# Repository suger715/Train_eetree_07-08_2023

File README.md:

# Train_eetree_07-08_2023
###From July to August 2023, I interned in some projects of Suzhou Hard Harvest Information Technology Company

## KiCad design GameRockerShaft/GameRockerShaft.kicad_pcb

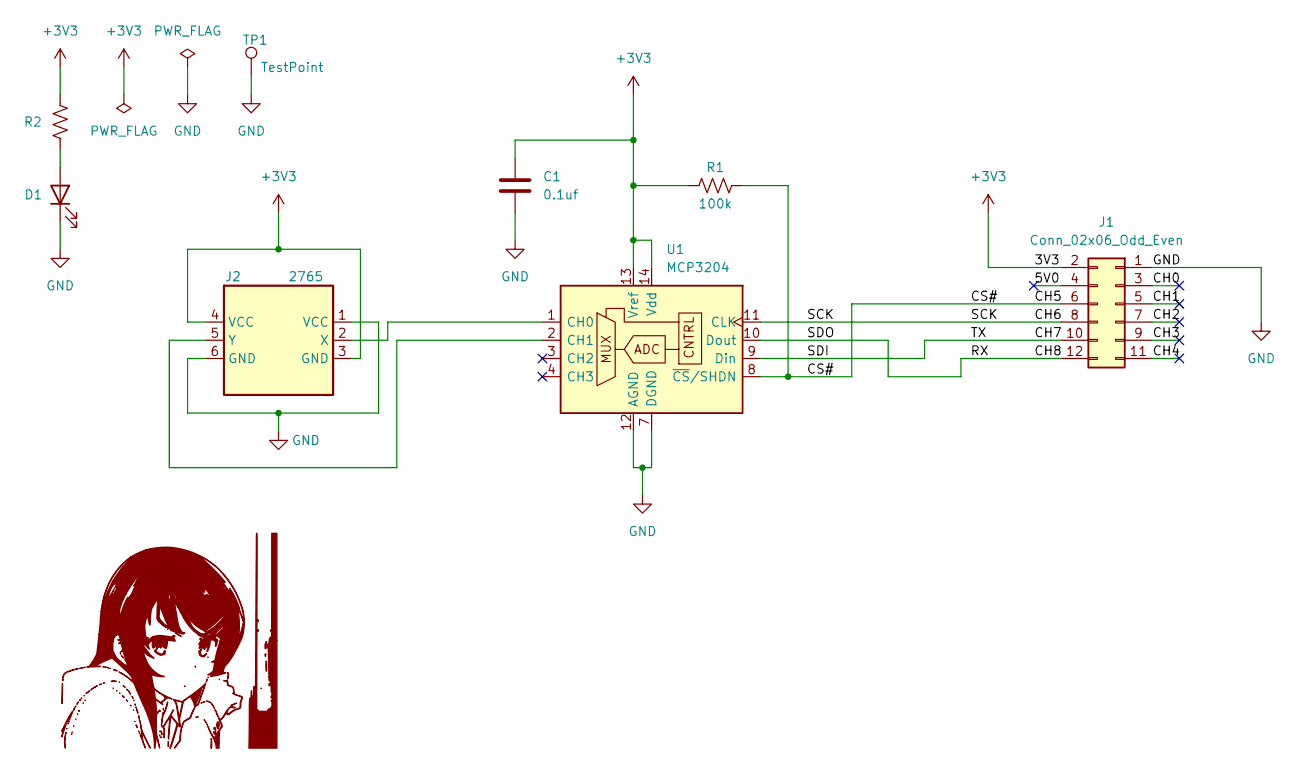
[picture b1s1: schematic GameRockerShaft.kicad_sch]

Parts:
C1: 0.1uf; C_0805_2012Metric
D1: PWR; LED_0805_2012Metric
J1: Conn_02x06_Odd_Even; PinSocket_2x06_P2.54mm_Horizontal
J2: 2765
R1: 100k; R_0805_2012Metric
R2: 470; R_0805_2012Metric
TP1: TestPoint; TestPoint_THTPad_1.5x1.5mm_Drill0.7mm
U1: MCP3204; SOIC-14_3.9x8.7mm_P1.27mm

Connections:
+3V3: C1.1, J1.2, J2.3 (GND), J2.4 (VCC), R1.1, R2.2, U1.13 (Vref), U1.14 (Vdd)
/5V0: J1.4
/CH0: J1.3
/CH1: J1.5
/CH2: J1.7
/CH3: J1.9
/CH4: J1.11
/CH5: J1.6, R1.2, U1.8 (~CS/SHDN)
/CH6: J1.8, U1.11 (CLK)
/CH7: J1.10, U1.9 (Din)
/CH8: J1.12, U1.10 (Dout)
GND: C1.2, D1.1 (K), J1.1, J2.1 (VCC), J2.6 (GND), TP1.1, U1.7 (DGND), U1.12 (AGND)
unnamed: D1.2 (A), R2.1
unnamed: J2.2 (X), U1.1 (CH0)
unnamed: J2.5 (Y), U1.2 (CH1)

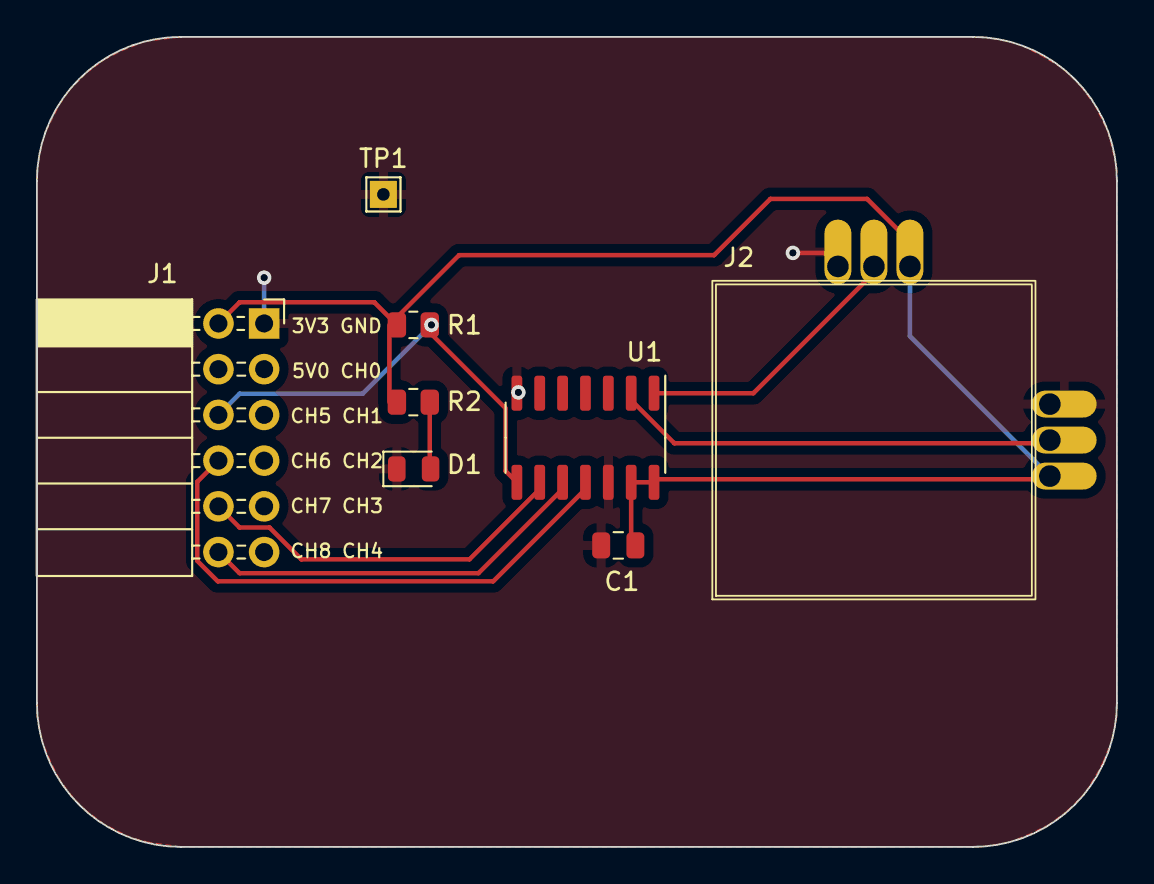
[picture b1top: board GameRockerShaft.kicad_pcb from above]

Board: 2 copper layers, 60.0 x 45.0 mm, 8 parts (0 on the bottom side), 9 nets.

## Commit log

2023-07-13 remove GameRocher
